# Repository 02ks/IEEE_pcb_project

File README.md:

***WIP***

# IEEE_pcb_project

IEEE PCB Project for Fall 2022

## To Do:

> Everything

## Have done:

> Set up GitHub Repo

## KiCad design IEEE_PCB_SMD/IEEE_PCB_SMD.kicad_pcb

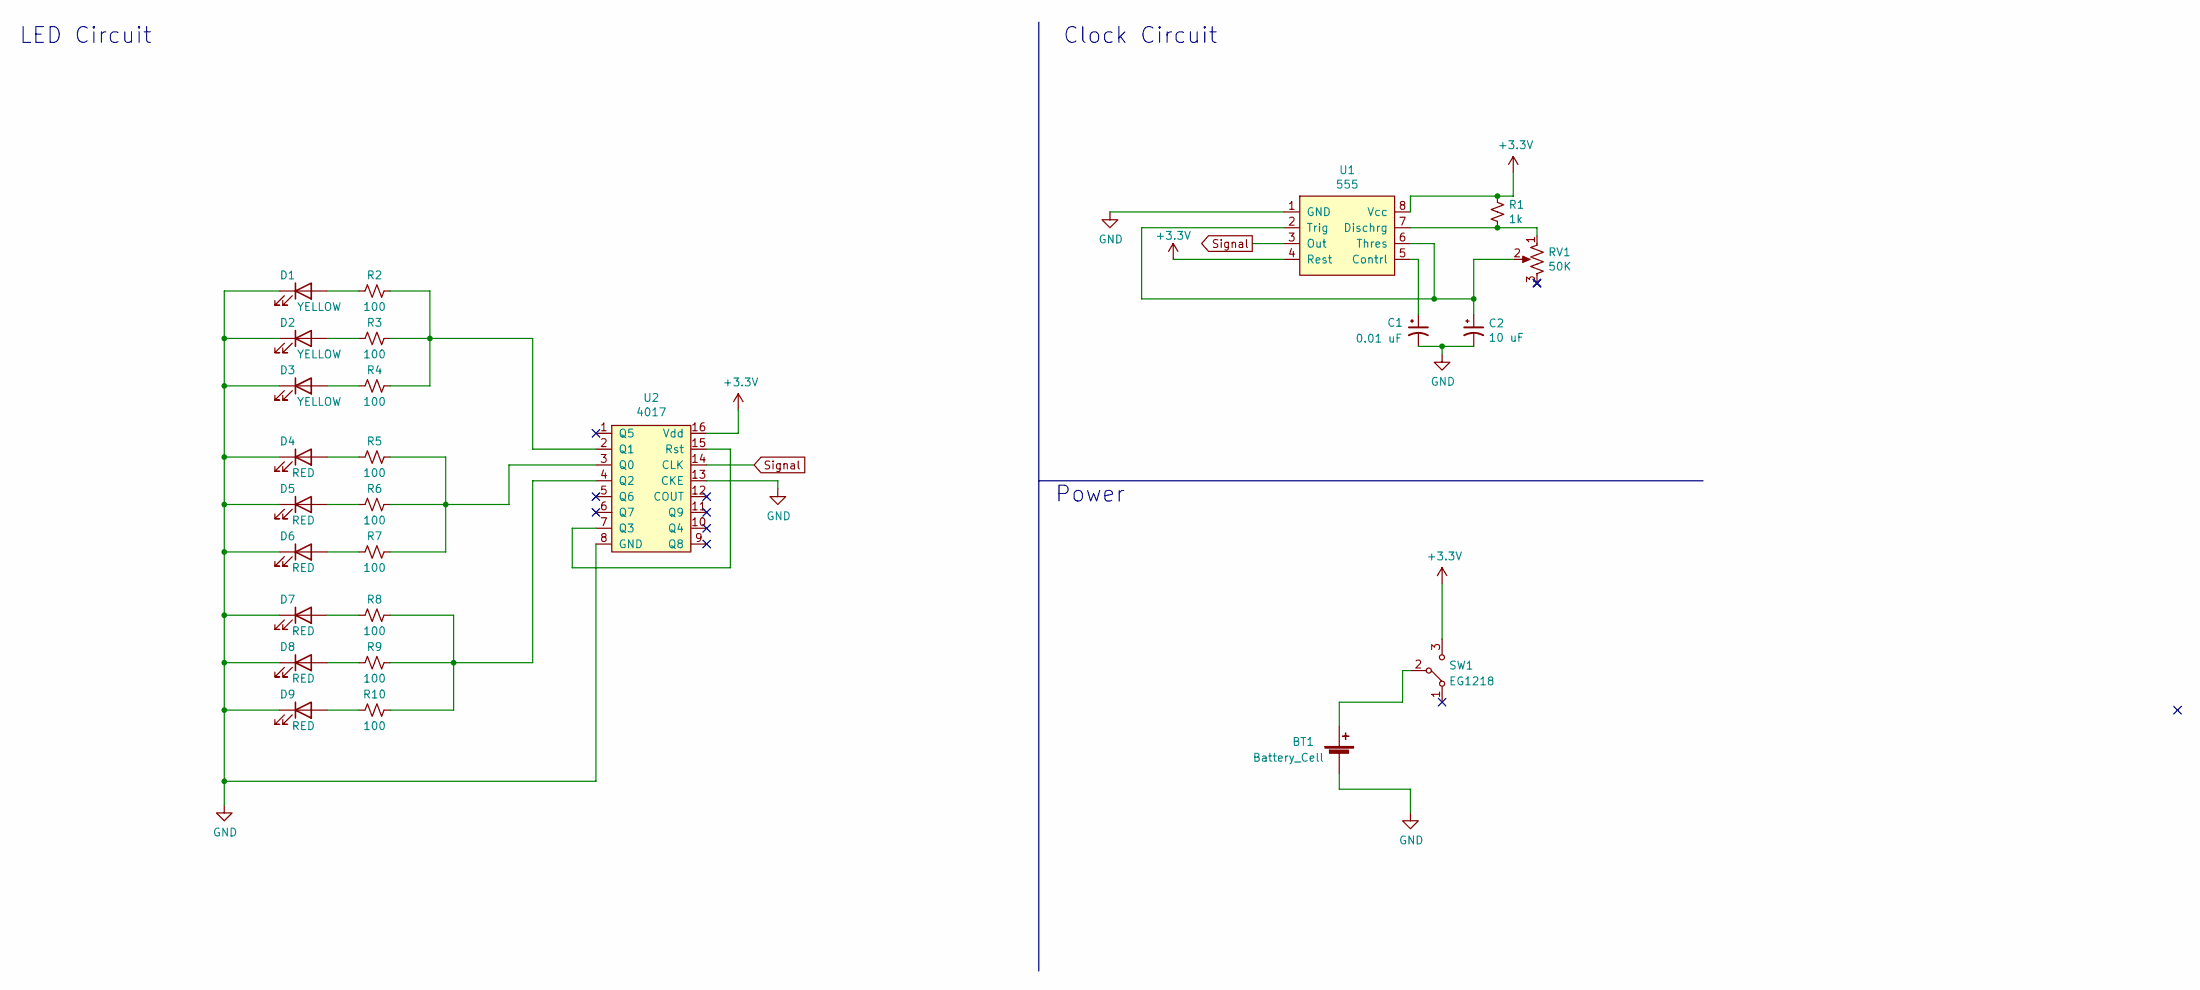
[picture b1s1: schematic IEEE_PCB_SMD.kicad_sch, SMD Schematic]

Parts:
BT1: Battery_Cell; CR2025TR
C1: 0.01 uF; CP_Radial_D5.0mm_P2.00mm
C2: 10 uF; CP_Radial_D5.0mm_P2.00mm
D1, D2, D3: YELLOW; IN-S63AT
D4, D5, D6, D7, D8, D9: RED; IN-S63AT
R1: 1k; R_Axial_DIN0207_L6.3mm_D2.5mm_P7.62mm_Horizontal
R2, R3, R4, R5, R6, R7, R8, R9, R10: 100; R_0603_1608Metric_Pad0.98x0.95mm_HandSolder
RV1: 50K; CT6EP504
SW1: EG1218
U1: 555
U2: 4017

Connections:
+3V3: R1.1, SW1.3, U1.4 (Rest), U1.8 (Vcc), U2.16 (Vdd)
GND: BT1.2 (-), C1.2, C2.2, D1.1 (K), D2.1 (K), D3.1 (K), D4.1 (K), D5.1 (K), D6.1 (K), D7.1 (K), D8.1 (K), D9.1 (K), RV1.3, U1.1 (GND), U2.8 (GND), U2.13 (CKE)
unnamed: BT1.1 (+), SW1.2
unnamed: C1.1, U1.5 (Contrl)
unnamed: C2.1, RV1.2, U1.2 (Trig), U1.6 (Thres)
unnamed: D1.2 (A), R2.2
unnamed: D2.2 (A), R3.2
unnamed: D3.2 (A), R4.2
unnamed: D4.2 (A), R5.2
unnamed: D5.2 (A), R6.2
unnamed: D6.2 (A), R7.2
unnamed: D7.2 (A), R8.2
unnamed: D8.2 (A), R9.2
unnamed: D9.2 (A), R10.2
unnamed: R1.2, RV1.1, U1.7 (Dischrg)
unnamed: R2.1, R3.1, R4.1, U2.2 (Q1)
unnamed: R5.1, R6.1, R7.1, U2.3 (Q0)
unnamed: R8.1, R9.1, R10.1, U2.4 (Q2)
unnamed: U2.7 (Q3), U2.15 (Rst)
Signal: U1.3 (Out), U2.14 (CLK)

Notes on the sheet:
Power
LED Circuit
Clock Circuit

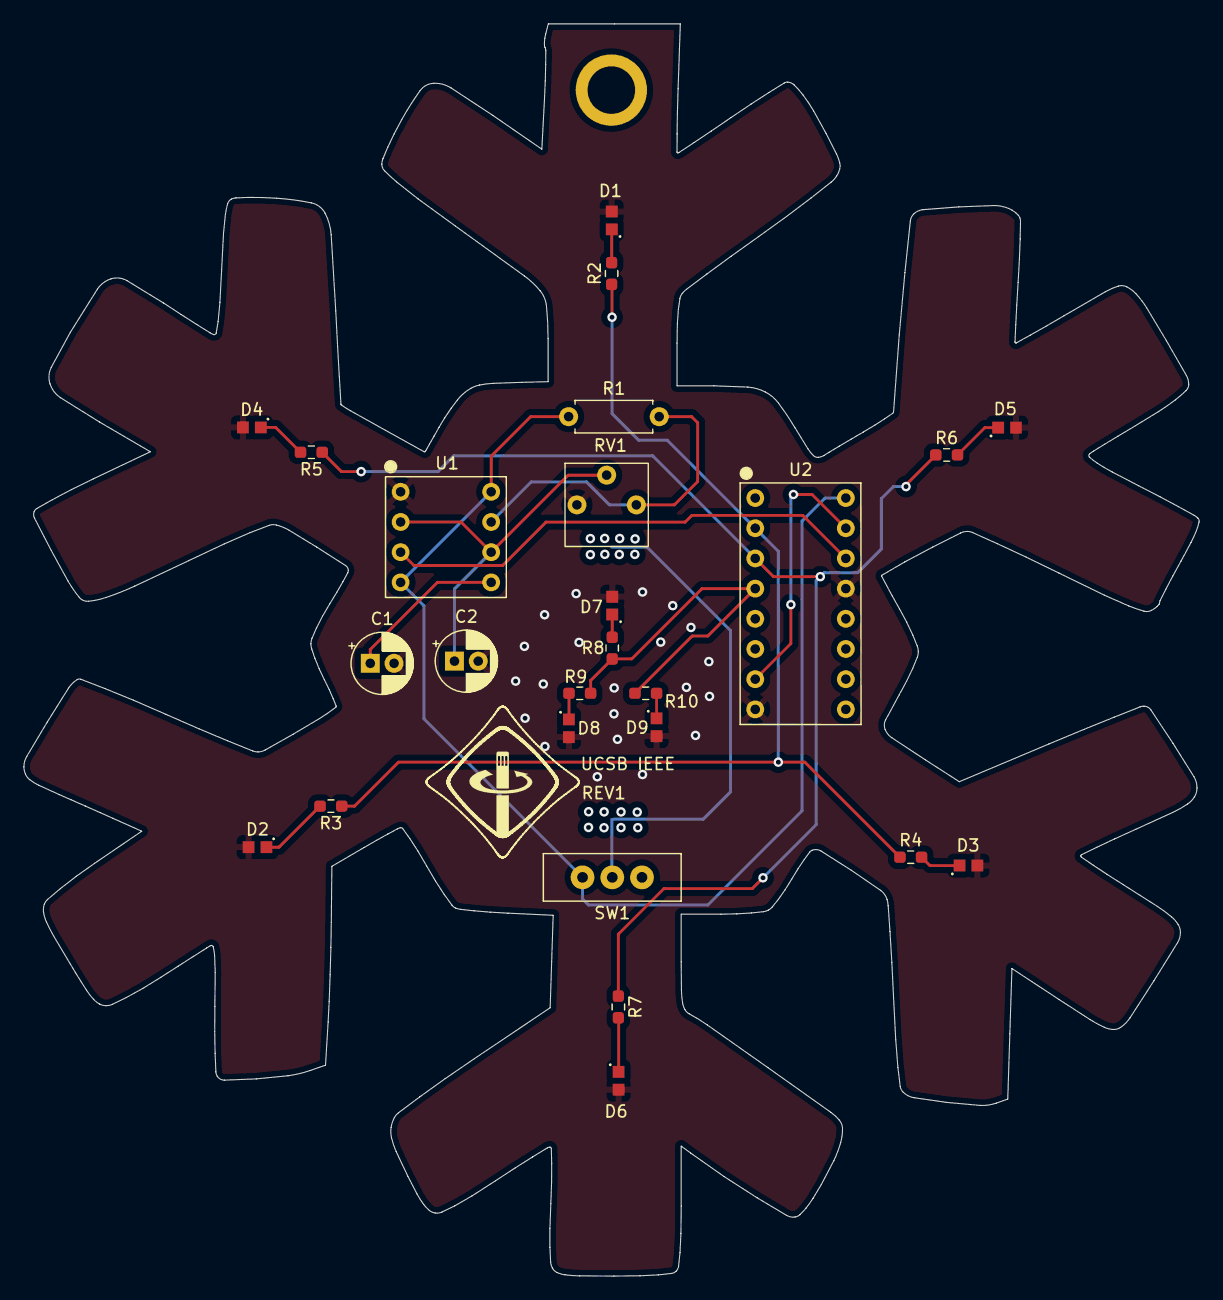
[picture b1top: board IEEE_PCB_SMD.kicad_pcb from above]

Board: 2 copper layers, 98.9 x 105.4 mm, 26 parts (0 on the bottom side), 20 nets.

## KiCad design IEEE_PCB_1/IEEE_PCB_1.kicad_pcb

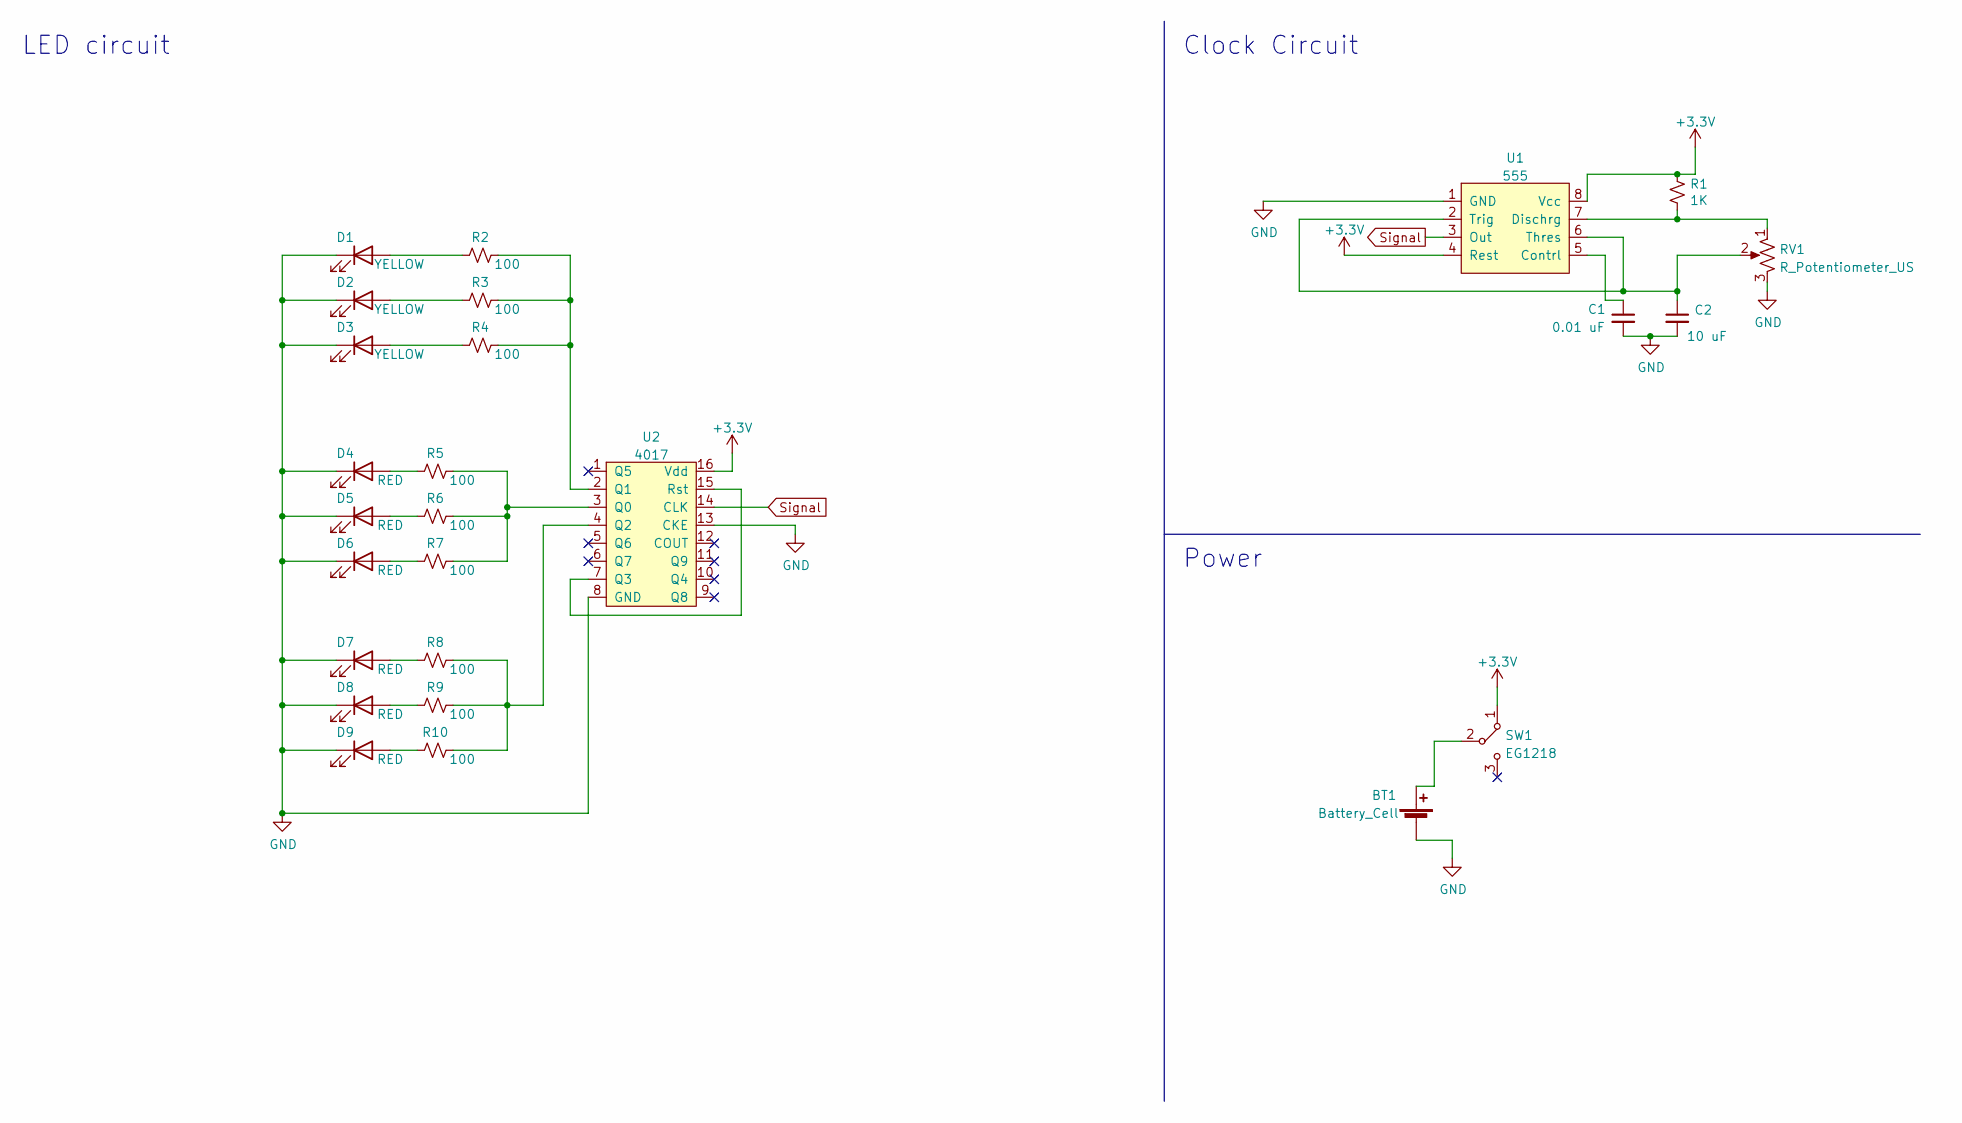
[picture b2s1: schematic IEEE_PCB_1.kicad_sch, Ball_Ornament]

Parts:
BT1: Battery_Cell; CR2025TR
C1: 0.01 uF; CP_Radial_D5.0mm_P2.00mm
C2: 10 uF; CP_Radial_D5.0mm_P2.00mm
D1, D2, D3: YELLOW; LED_D5.0mm_Clear
D4, D5, D6, D7, D8, D9: RED; LED_D5.0mm_Clear
R1: 1K; R_Axial_DIN0207_L6.3mm_D2.5mm_P7.62mm_Horizontal
R2, R3, R4, R5, R6, R7, R8, R9, R10: 100; R_0603_1608Metric_Pad0.98x0.95mm_HandSolder
RV1: R_Potentiometer_US; CT6EP504
SW1: EG1218
U1: 555
U2: 4017

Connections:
+3.3V: R1.1, SW1.1, U1.4 (Rest), U1.8 (Vcc), U2.16 (Vdd)
GND: BT1.2 (-), C1.2, C2.2, D1.1 (K), D2.1 (K), D3.1 (K), D4.1 (K), D5.1 (K), D6.1 (K), D7.1 (K), D8.1 (K), D9.1 (K), RV1.3, U1.1 (GND), U2.8 (GND), U2.13 (CKE)
unnamed: BT1.1 (+), SW1.2
unnamed: C1.1, U1.5 (Contrl)
unnamed: C2.1, RV1.2, U1.2 (Trig), U1.6 (Thres)
unnamed: D1.2 (A), R2.1
unnamed: D2.2 (A), R3.1
unnamed: D3.2 (A), R4.1
unnamed: D4.2 (A), R5.1
unnamed: D5.2 (A), R6.1
unnamed: D6.2 (A), R7.1
unnamed: D7.2 (A), R8.1
unnamed: D8.2 (A), R9.1
unnamed: D9.2 (A), R10.1
unnamed: R1.2, RV1.1, U1.7 (Dischrg)
unnamed: R2.2, R3.2, R4.2, U2.2 (Q1)
unnamed: R5.2, R6.2, R7.2, U2.3 (Q0)
unnamed: R8.2, R9.2, R10.2, U2.4 (Q2)
unnamed: U2.7 (Q3), U2.15 (Rst)
Signal: U1.3 (Out), U2.14 (CLK)

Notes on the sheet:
LED circuit
Clock Circuit
Power

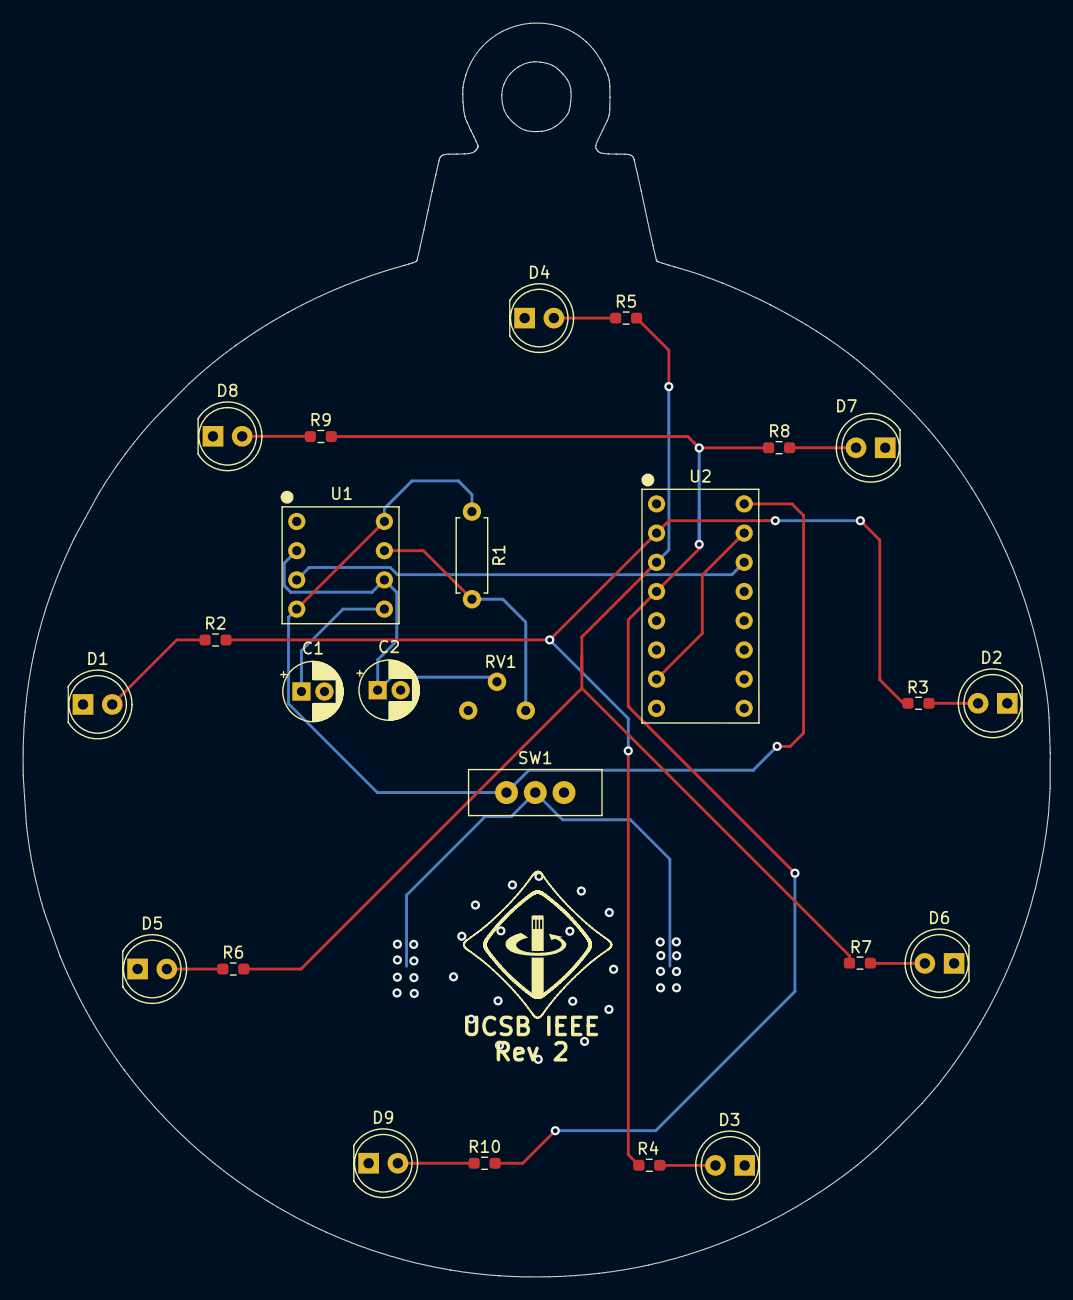
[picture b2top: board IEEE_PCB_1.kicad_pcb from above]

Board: 2 copper layers, 89.3 x 109.0 mm, 26 parts (0 on the bottom side), 20 nets.

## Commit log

2022-06-22 added KiCad file (testing)
2022-07-24 Summary
    Added Schematic
2022-08-03 Rev2
    Made more changes to the schematic. Will start the footprints soon
2022-08-04 Footprints edits
    Finished custom footprints. Will need to review copper through-hole measurements
2022-08-05 Footprint assignment
    assigned the custom symbols with the custom symbols. Still waiting for standard parts
2022-08-07 Rev3
    editted the LEDs
2022-08-07 Added Ball Ornament Outline
2022-08-07 Added Snowflake Outline
2022-08-08 Changed edge cuts
2022-08-08 update
    e
2022-08-08 added .DXF files
2022-08-08 Added Outlines to Library
2022-08-08 pull
    pushin p
2022-08-12 Rev4
    finished potentiometer footprint
2022-08-13 PCB
    first pcb ball orientation
2022-08-13 SMD LED
2022-08-13 Rev5
2022-08-14 Update fp-info-cache
2022-08-14 SMD rev
2022-08-28 silkscreen outline in progress
2022-09-05 SMD Rev2
2022-09-06 PCB rev smd
2022-09-08 SMD Rev3
2022-09-09 Rev4 SMD
2022-09-09 Rev5 SMD
2022-09-09 same
2022-09-11 Rev5
    new ball ornament design
2022-09-12 changed silkscreen
    forgot to push
2022-09-24 deleted silkscreen
2022-09-24 Rev4
2022-09-24 dsalkf
2022-09-25 changed trace
2022-09-25 edit traces
    one trace too close to edge
2022-10-08 Rev 10/8/22
    changed the logo footprint
    changed the resistor footprint
    added more vias to the power
    altered traces to better fit the ESR standards
2022-10-09 Rev - Matthew
    Snowflake changes:
    Fixed battery and switch symbols
    added 100 ohm resistors 603
    looked at traces - not acid traps that I see
    will work on the ball soon
2022-10-09 rev - Matthew
    editted the ball ornament
    added resistors
    fixed any battery and switch symbols
    fixed any acid traps
2022-10-22 New Changes
2022-10-22 Demo(Test)
2022-11-02 RV1 changes
2022-11-08 changed demo
2022-11-09 added updated footprints
2022-11-09 deleted gbr files
2022-11-15 update schematic, pot footprint
